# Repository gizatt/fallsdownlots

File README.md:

# FallsDownLots

<details>
  <summary>Click to expand more demo GIFs</summary>

</details>

## About
This project ("FallsDownLots") is a 2-wheeled balancing robot designed around two brushless DC (BLDC) gimbal motors, controlled with field-oriented control. Previous iterations of wheeled balancing robots I've built have been plagued by issues with poor motor control (primarily backlash, inertia, and friction causing shaky control around the upright fixed point). This project instead uses a high-torque (specifically low KV / high winding count) 3-phase motor, paired with an absolute magnetic encoder to determine the shaft angle, and a 3-phase drive circuit to deliver current. With some pretty simple parts, I've been able to get something pretty close to actual torque control for the wheels of this robot, and it's been pretty easy to tune up for smooth, stable, remote-controllable operation.

For ease of control tuning, I chose a main board with Bluetooth Low-Energy (BLE) support, and written a companion program that connects to the robot and allows parameter updates. This program is currently very primitive but it beats reprogramming or having it drag around a serial cable (which interferes with control).

I mostly rely on [SimpleFOC](https://simplefoc.com/) for the actual FOC implementation, and took their advice on sensor and drive chip choice. I'd like to dive deeper into controlling these motors better -- for example, trying to compensate for cogging torque to get smoother operation - but I have more fundamental issues to fix first (see below).

- For code, see the `fallsdownlots` subdirectory (which is a PlatformIO package).
- For CAD, see [Onshape](https://cad.onshape.com/documents/34e0d9ef519aef4b34c19df6/w/b4fc20d7f51a03280199ecb2/e/801a65f226a9bb9fc692247b?renderMode=0&uiState=648a75b56f21326dd5086d67). Sorry it's not organized into a main assembly yet, this is just my 3D print part workshop. Approximately up-to-date STLS are in the `stls` subdirectory. Print `MotorMount` twice, mirroring one of them. Print `Wheel` twice. Print `Tire` twice in TPU or another tacky, flexible filament.
- For PCB design and electrical schematics, see `board_v2` subdirectory (which is a KiCad project).

## Diagram and Parts List

(Note: this references a special-edition physically packaged version of this robot.)

Parts list:
- 2X PLA wheel with TPU tire
- 2x Motor assembly, composed of...
  - 1x PLA Wheel + TPU tire
  - 1x PLA Motor Mount
  - 1x AS5600 Breakout Board
  - 1X 2204-260KV BLDC Motor (with 3-pin JST RE connector)
  - 1X 10KOhm Thermistor
  - 1X JST MX 6-pin Male Connector
- 1x Altoid tin case with lid, containing...
  - 1x PLA board mounting backplate, already attached to case.
  - 1x Main electronics board
  - 4x M3x8mm hex bolts and nuts
  - 8x M2x4mm hex bolts
  - 3x M2x8mm self-tapping phillips screws
  - Spare parts: M3x8mm self-tapping phillips screws, plus other screw types, plus spare TPU tire

Not included (supply seperately):
- 1x 400Mah 2S LiPO [[Amazon link](https://www.amazon.com/gp/product/B072BH1XP6/ref=ox_sc_act_title_1?smid=A10R5CWYCW5T5E&psc=1)] and balance charger.
- 1.5 and 2.5 metric alley keys
- Small phillips head screwdriver
- Small narrow / needle-nose pliers
- Non-ancient bluetooth adapter (probably needs BLE >= 5.1?)

## Assembly Instructions

Assembly is simple, but the tight packaging makes assembly pretty order-sensitive.

1) Attach the motor assemblies onto the bottom of the case, as shown, using 4x M3x8mm hex bolts and nuts. Before you fully attach these, pass their wires into the case through the nearby holes; otherwise it'll be a tight fit to get those wires passed in, especially with the electronics board mounted. Be reasonably gentle with the wires...

2) Now install the main electronics board by sliding it into place and installing the 3x M2x8mm self-tapping phillips screws, which screw into posts on the PLA backplate. Note that you want the wires from the motor assemblies *over* the main board once it's installed -- it's a bit of dance to get it everything into place.
3) Plug in the wires from the motor assemblies into the plugs on their corresponding side. See picture for exact orientation of wires -- carefully note the orientation of the 3-pin motor connectors! If you get this backwards, the motors will spin the wrong way. I recommend some good needlenose pliers to help with wrangling and attaching these cables.

4) Attach the tires to the motors with at least 2x M2x4mm hex bolts each. These bolts should be snug but don't go ham (the PLA may not be able to take it).
5) Slide the battery into the space under the on-off switch with the cables facing left, and plug in the cable, being careful to have the red wire on the right. *This board technically has reverse bias protection but I have never tested it and I do not want you to either.*

Troubleshooting: contact me!

### Motor assembly internals

I packaged this robot with each motor and sensor already assembled, since their assembly is a bit sensitive, but you're welcome to disassemble and take a look. These assemblies are pancakes of a tiny BLDC motor ([Amazon link](https://www.amazon.com/DAUERHAFT-Brushless-Efficiency-Drones-Gimbal/dp/B08S5JSD3Q/ref=sr_1_4?crid=16NAYMQDO30CI&keywords=bldc+8605&qid=1686794765&sprefix=bldc+860%2Caps%2C130&sr=8-4), though this unit is much cheaper on Aliexpress) with a magnet superglued to its shaft, an [absolute magnetic encoder](https://www.amazon.com/Magnetic-Encoder-Induction-Measurement-Precision/dp/B094F8H591/ref=sr_1_2?crid=1PB3J5XDUXQNP&keywords=magnetic+encoder&qid=1686794826&sprefix=magnetic+encod%2Caps%2C122&sr=8-2) on a breakout board, and a thermistor sandwiched between them.

## Usage instructions

Flip the switch to the right to turn on. I recommend laying the robot down or standing it on its head during startup; each wheel will independent move a quarter rotation back and forth during startup as a calibration routine (this is managed by SimpleFOC). Once that is done, the robot should be active, and will attempt to balance to the upright if it is within ~60 degrees of upright. The easiest way to get it going is to go to a clear area of floor, holding it sideways, and confidentally and quickly place it roughly upright and let go. The integrators reset and motors turn off again when it is not upright, e.g. if it falls.

I recently discovered another fun demo method that happens to work, despite the control algorithm not being created with this in mind: hold the robot by the wheels, and swing the robot upright. It should catch itself at the upright and stabilize there. See [this video](media/flipup_demo.gif).

Note: there's a few bugs somewhere in the code, especially in the BLE stuff, and sometimes the IMU or magnetic encoders get into weird states and stop talking. If the robot suddenly stops and falls over, or otherwise seems unresponsive, just do a complete power cycle. This is more likely to happen if you're using one of the BLE scripts, proportional to how much data you're sending/receiving.

## Control details

The main control code is implemented in `main-fallsdownlots.cpp::do_control`. I'm currently running a PID loop on angle, with the zero angle estimated via a low-pass filter on the measured angle (which assumes we stabilize on average to the upright), plus a PI loop on wheel velocity, plus a PI loop on yaw velocity. These are all controlled by parameters in the `ControlParams` struct.

There are two Python scripts in the `fallsdownlots/scripts` folder. Both connect to the robot with BLE.
- `communicator.py`: Once connected, type a command of the format "<param name> <float value>" and hit enter, and it'll send it to the robot. It should echo the new setting back, though sometimes it takes a while to come back. If you just send "<param name>" without a value, it'll send the current value back. Example: "ANG_D 0.1" changes the derivative gain to 0.1. Ignore the plot window that opens up, it doesn't work yet...
- `gamepad.py`: Connects to the robot and sends commands (adjusting the setpoints of the velocity and yaw velocity control loops) in response to the arrow keys, letting you control the robot. Hold shift while pressing arrow keys to go faster. There's a mode to display robot odometry (see code) but it's currently super sketchy.

## Notes / Thoughts

### TODOs
- Major code cleanup. Tons of cruft left here I haven't re-orged.
- Use BLE interface to create an interactive motor teststand for tuning up actual motor control loops.

### Stuff that didn't work as well as I hoped
- Because I'm talking to 2 magnetic encoders and 1 IMU over relatively slow I2C (800khz, I think), I haven't been able to get my main control loop to run faster than ~200hz. I'm configuring the IMU to do its own high-rate on-board orientation estimation, so that's fine -- but this low rate makes it hard to drive the motors in anything other than torque mode (velocity and position mode go unstable pretty easily / can't be tuned to be too accurate as my loop rate is probably too low), and I can't crank the actual control gains as high as I'd like for tight tracking without inducing oscillations. It's possible I can get info from at least the magnetic encoders over their analog output instead... but I would need to experiment with that.
- I'm relying on Bluetooth Low-Energy as my wireless comms media, but I'm finding the bandwidth super low, and the code on the embedded side super crash-prone. I'm probably overloading buffers somewhere and configuring stuff wrong... next time, I'm just gonna have the robot connect to my Wifi. I'd rather deal with networking gremlins I sort of understand than BLE ones I don't.

### BLE Comms Protocol

The robot sends a 36-byte (+COBS-encoding) packet over BLE UART at ~30hz consisting of 8 floats:
```
[pitch, yaw, d_pitch, d_yaw, odometry, l_cmd, r_cmd, max_motor_temp]
```

On-board, the robot has a registry of named control parameters that you can write with a command formatted:
```
<NULL-TERMINATED-NAME>[optional single float]
```
and the robot will respond with a similarly formatted message (+COBS-encoding) packet with a single float indicating the updated value, or the current value if you didn't include the float value.

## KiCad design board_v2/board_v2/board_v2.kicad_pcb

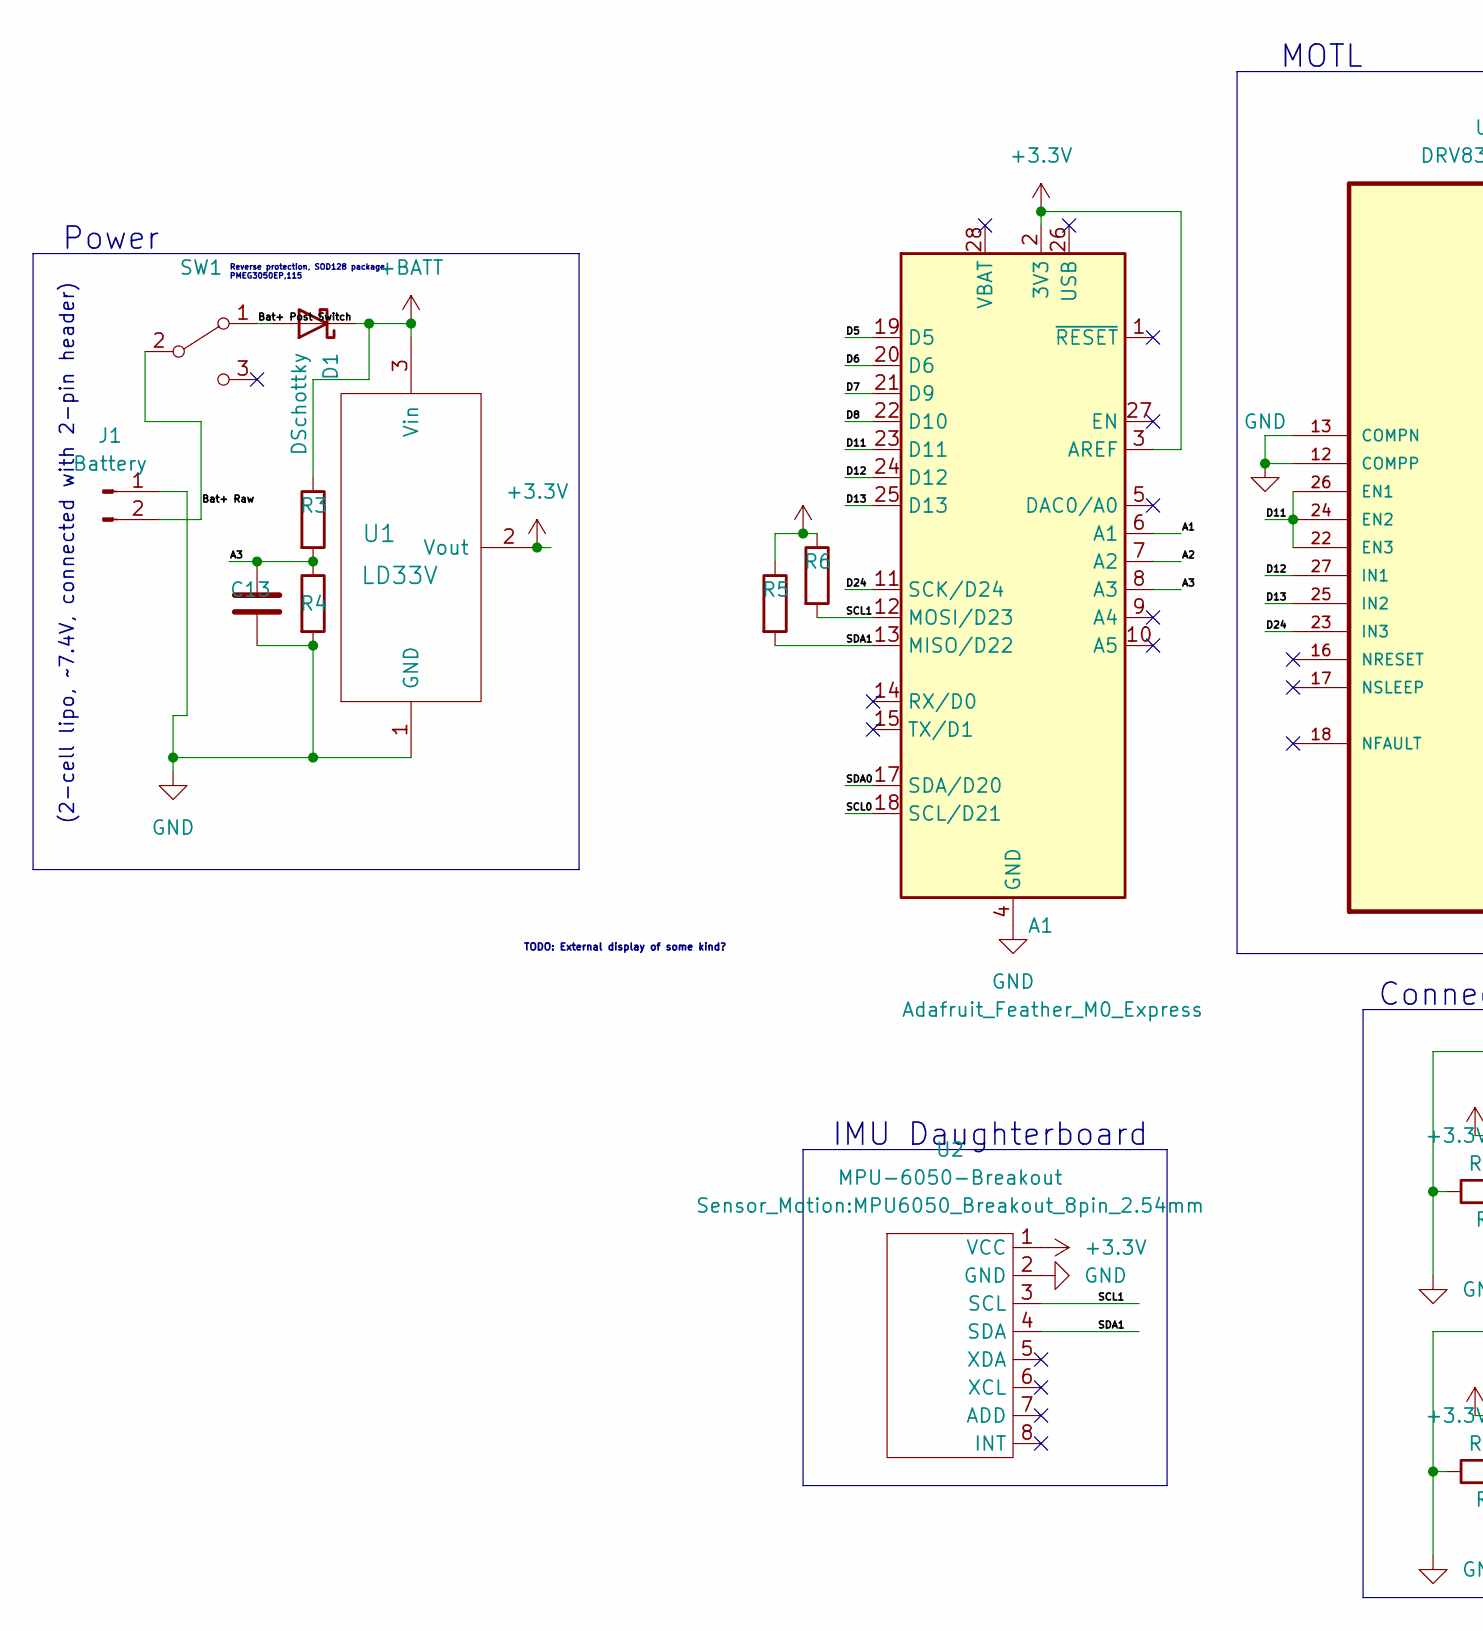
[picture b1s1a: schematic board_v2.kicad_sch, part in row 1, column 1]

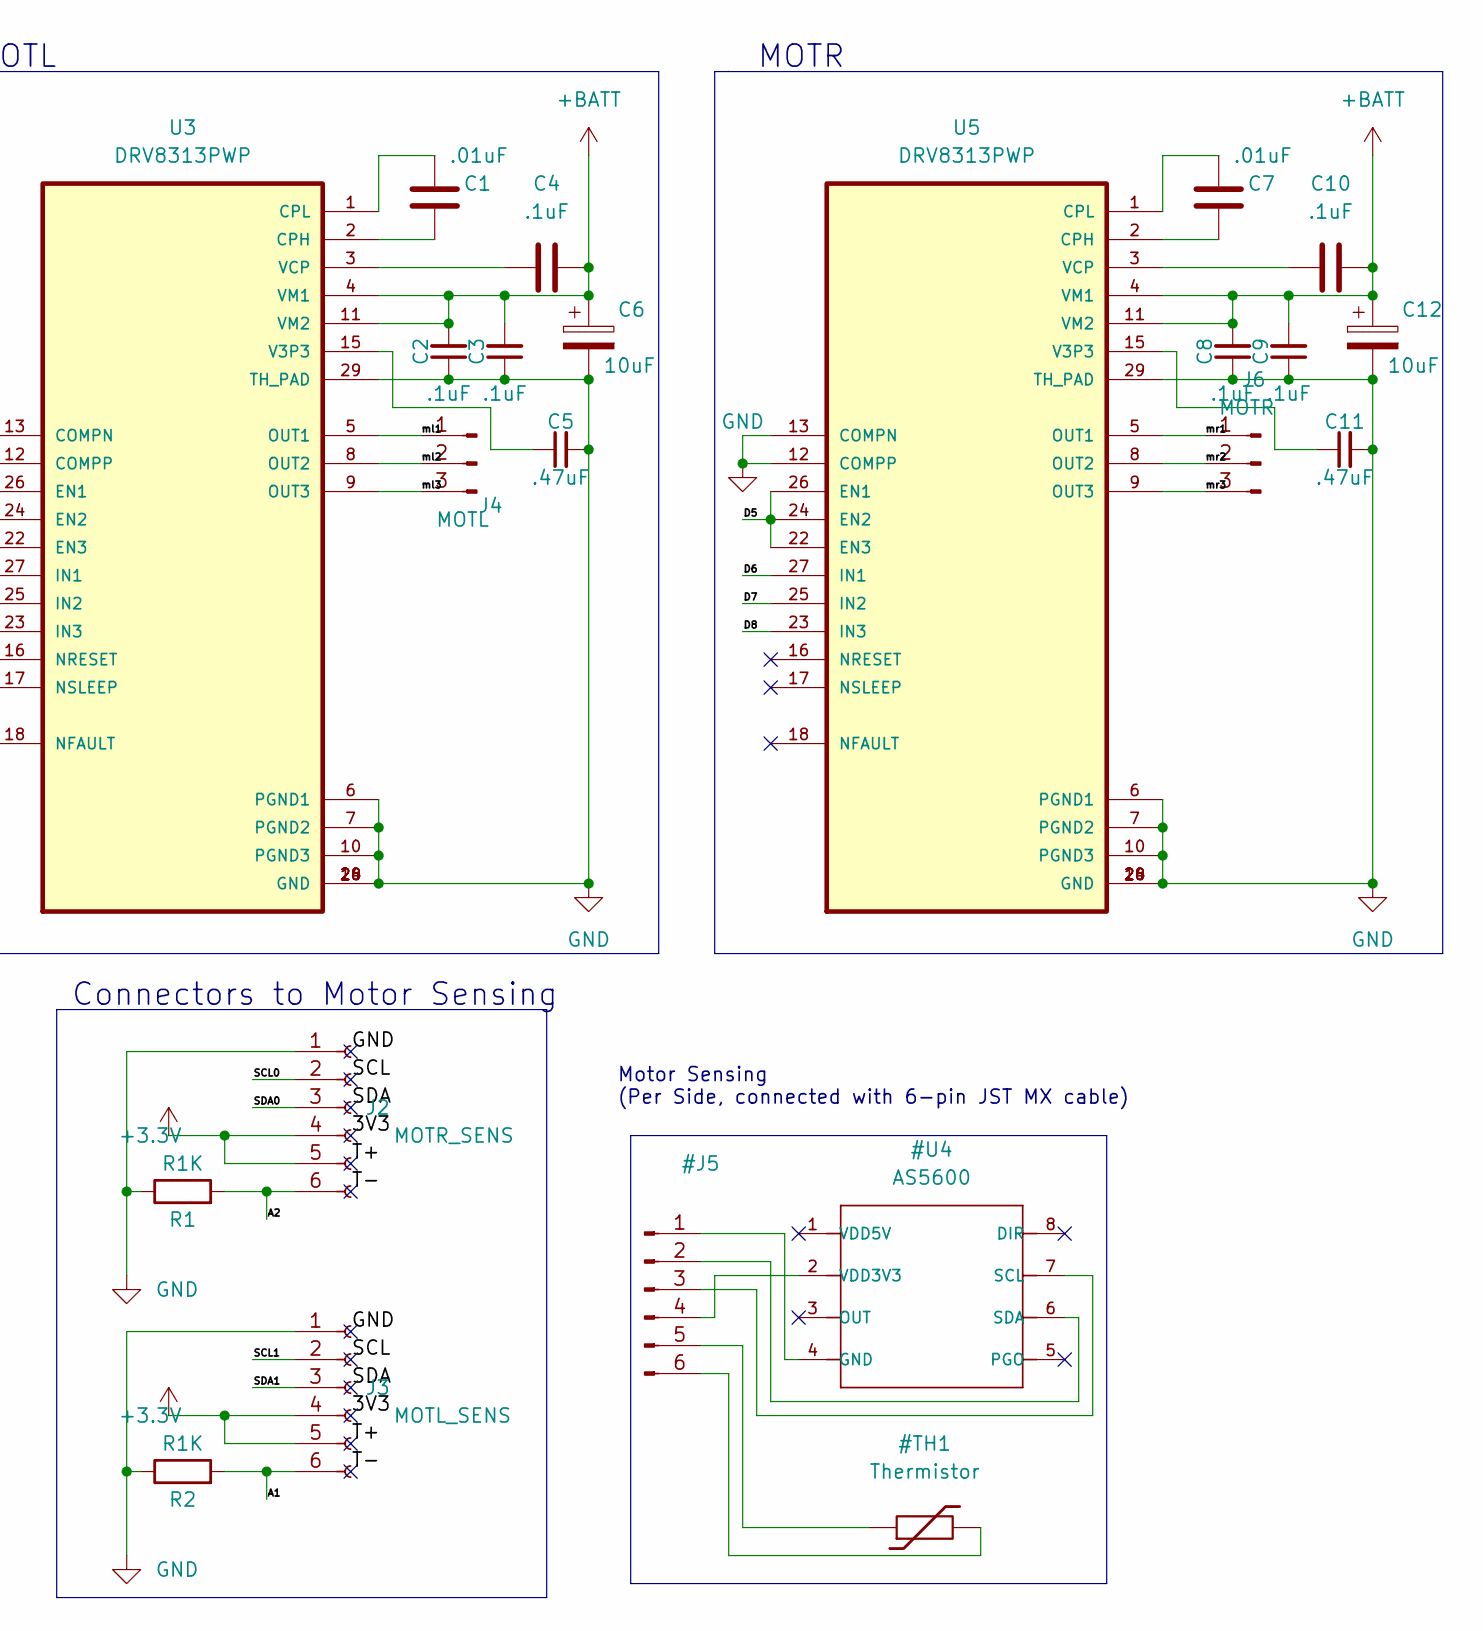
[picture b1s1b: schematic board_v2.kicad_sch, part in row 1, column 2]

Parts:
A1: Adafruit_Feather_M0_Express; Adafruit_Feather_M0_Wifi_WithMountingHoles
C1, C7: .01uF; C_0805_2012Metric_Pad1.18x1.45mm_HandSolder
C2, C3, C4, C8, C9, C10: .1uF; C_0805_2012Metric_Pad1.18x1.45mm_HandSolder
C5, C11: .47uF; C_0805_2012Metric_Pad1.18x1.45mm_HandSolder
C6, C12: 10uF; CP_Radial_D5.0mm_P2.50mm
C13: (no value)
D1: DSchottky; D_SOD-128
J1: Battery; PinHeader_1x02_P2.54mm_Horizontal
J2: MOTR_SENS; JST MX x6
J3: MOTL_SENS; JST MX x6
J4: MOTL; PinHeader_1x03_P2.54mm_Horizontal
J6: MOTR; PinHeader_1x03_P2.54mm_Horizontal
R1, R2: R1K; R_0805_2012Metric_Pad1.20x1.40mm_HandSolder
R3, R4, R5, R6: (no value)
SW1: (no value)
U1: LD33V; TO-220-3_Horizontal_TabDown
U2: MPU-6050-Breakout; MPU6050_Breakout_8pin_2.54mm
U3, U5: DRV8313PWP; IC_TPS61196PWPRQ1

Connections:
+BATT: C2.2, C3.2, C4.2, C6.1, C8.2, C9.2, C10.2, C12.1, D1.1 (K), R3.1, U1.3 (Vin), U3.4 (VM1), U3.11 (VM2), U5.4 (VM1), U5.11 (VM2)
/A1: A1.6 (A1), J3.6, R2.2
/A2: A1.7 (A2), J2.6, R1.2
/A3: A1.8 (A3), C13.1, R3.2, R4.1
/Bat+ Post Switch: D1.2 (A), SW1.1 (A)
/Bat+ Raw: J1.2, SW1.2 (B)
/D5: A1.19 (D5), U5.22 (EN3), U5.24 (EN2), U5.26 (EN1)
/D6: A1.20 (D6), U5.27 (IN1)
/D7: A1.21 (D9), U5.25 (IN2)
/D8: A1.22 (D10), U5.23 (IN3)
/D11: A1.23 (D11), U3.22 (EN3), U3.24 (EN2), U3.26 (EN1)
/D12: A1.24 (D12), U3.27 (IN1)
/D13: A1.25 (D13), U3.25 (IN2)
/D24: A1.11 (SCK/D24), U3.23 (IN3)
/SCL0: A1.18 (SCL/D21), J2.2
/SCL1: A1.12 (MOSI/D23), J3.2, R6.2, U2.3 (SCL)
/SDA0: A1.17 (SDA/D20), J2.3
/SDA1: A1.13 (MISO/D22), J3.3, R5.2, U2.4 (SDA)
/ml1: J4.1, U3.5 (OUT1)
/ml2: J4.2, U3.8 (OUT2)
/ml3: J4.3, U3.9 (OUT3)
/mr1: J6.1, U5.5 (OUT1)
/mr2: J6.2, U5.8 (OUT2)
/mr3: J6.3, U5.9 (OUT3)
GND: A1.4 (GND), A1.16 (GND), C2.1, C3.1, C5.2, C6.2, C8.1, C9.1, C11.2, C12.2, C13.2, J1.1, J2.1, J3.1, R1.1, R2.1, R4.2, U1.1 (GND), U2.2 (GND), U3.6 (PGND1), U3.7 (PGND2), U3.10 (PGND3), U3.12 (COMPP), U3.13 (COMPN), U3.14 (GND), U3.20 (GND), U3.28 (GND), U3.29 (TH_PAD), U5.6 (PGND1), U5.7 (PGND2), U5.10 (PGND3), U5.12 (COMPP), U5.13 (COMPN), U5.14 (GND), U5.20 (GND), U5.28 (GND), U5.29 (TH_PAD)
unnamed: C1.1, U3.1 (CPL)
unnamed: C1.2, U3.2 (CPH)
unnamed: C4.1, U3.3 (VCP)
unnamed: C5.1, U3.15 (V3P3)
unnamed: C7.1, U5.1 (CPL)
unnamed: C7.2, U5.2 (CPH)
unnamed: C10.1, U5.3 (VCP)
unnamed: C11.1, U5.15 (V3P3)

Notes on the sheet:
Power
TODO: External display of some kind?
IMU Daughterboard
MOTL
Motor Sensing (Per Side, connected with 6-pin JST MX cable)
MOTR
(2-cell lipo, ~7.4V, connected with 2-pin header)
Connectors to Motor Sensing
Reverse protection, SOD128 package, PMEG3050EP,115

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
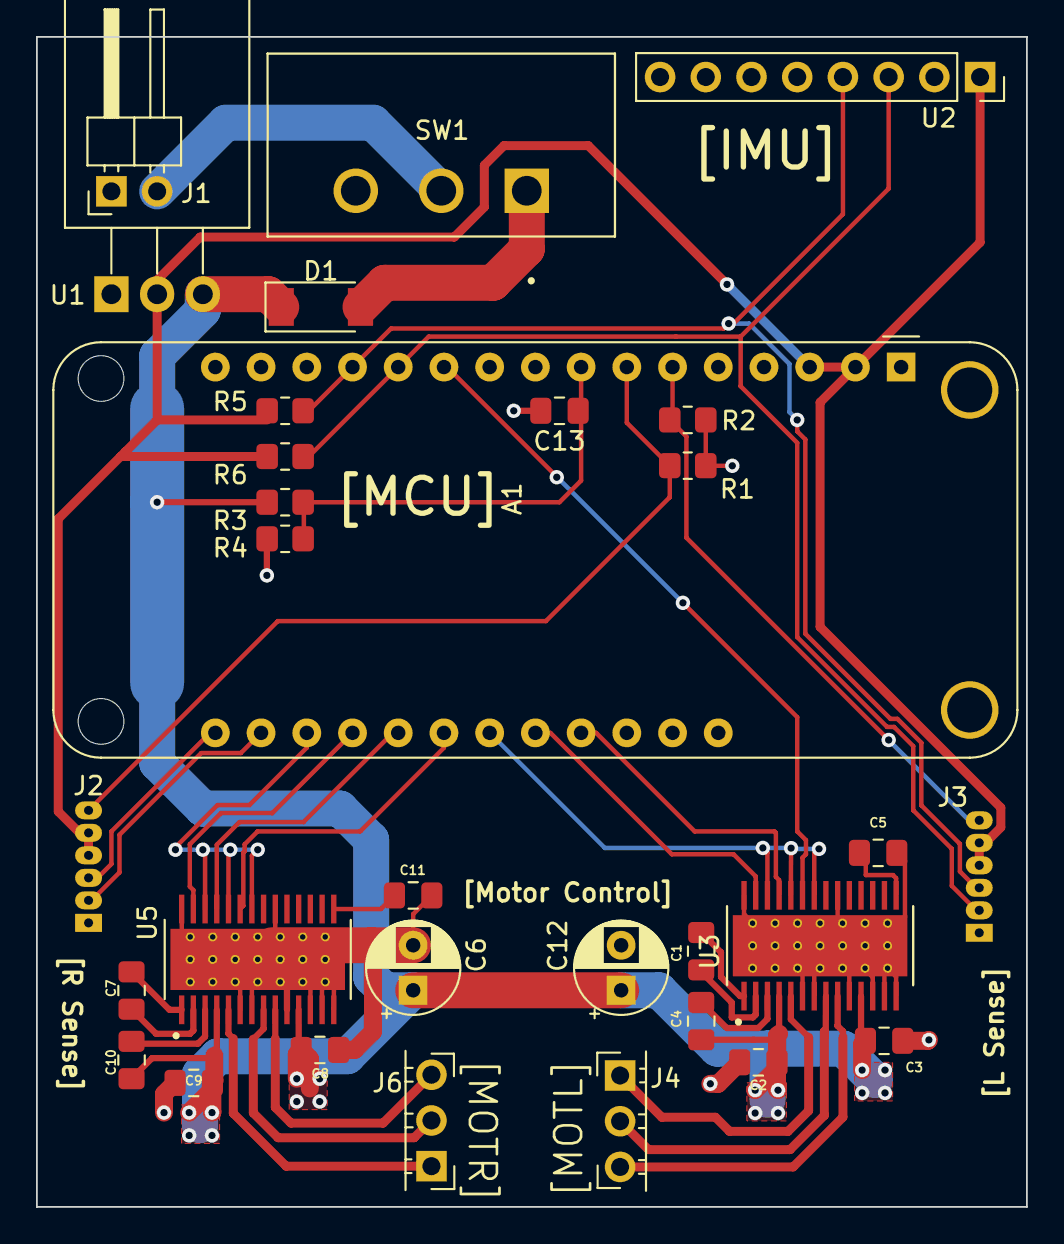
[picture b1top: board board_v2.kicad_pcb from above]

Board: 2 copper layers, 55.0 x 65.0 mm, 31 parts (0 on the bottom side), 34 nets.

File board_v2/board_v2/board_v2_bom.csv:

"Source:","C:\Users\Greg Izatt\src\fallsdownlots\board_v2\board_v2\board_v2.kicad_sch"
"Date:","6/4/2023 8:46:51 PM"
"Tool:","Eeschema 7.0.1"
"Generator:","C:\Program Files\KiCad\7.0\bin\scripting\plugins/bom_csv_grouped_by_value.py"
"Component Count:","35"

"Collated Components:"

"Item","Qty","Reference(s)","Value","LibPart","Footprint","Datasheet","DNP"
"1","1","A1","Adafruit_Feather_M0_Express","MCU_Module:Adafruit_Feather_Generic","Module:Adafruit_Feather","https://cdn-learn.adafruit.com/downloads/pdf/adafruit-feather.pdf",""
"2","2","C1, C7",".01uF","Device:C","Capacitor_SMD:C_0805_2012Metric_Pad1.18x1.45mm_HandSolder","~",""
"3","4","C2, C3, C8, C9",".1uF","Device:C_Small","Capacitor_SMD:C_0805_2012Metric_Pad1.18x1.45mm_HandSolder","~",""
"4","3","C4, C10, C13",".1uF","Device:C","Capacitor_SMD:C_0805_2012Metric_Pad1.18x1.45mm_HandSolder","~",""
"5","2","C5, C11",".47uF","Device:C_Small","Capacitor_SMD:C_0805_2012Metric_Pad1.18x1.45mm_HandSolder","~",""
"6","2","C6, C12","10uF","Device:C_Polarized","Capacitor_THT:CP_Radial_D5.0mm_P2.50mm","~",""
"7","1","D1","DSchottky","Device:D_Schottky","Diode_SMD:D_SOD-128","~",""
"8","1","J1","Battery","Connector:Conn_01x02_Male","Connector_PinHeader_2.54mm:PinHeader_1x02_P2.54mm_Horizontal","~",""
"9","1","J2","MOTR_SENS","Connector:Conn_01x06_Female","Connector:JST MX x6","~",""
"10","1","J3","MOTL_SENS","Connector:Conn_01x06_Female","Connector:JST MX x6","~",""
"11","1","J4","MOTL","Connector:Conn_01x03_Male","Connector_PinHeader_2.54mm:PinHeader_1x03_P2.54mm_Horizontal","~",""
"12","1","J6","MOTR","Connector:Conn_01x03_Male","Connector_PinHeader_2.54mm:PinHeader_1x03_P2.54mm_Horizontal","~",""
"13","2","R1, R2","R1K","Device:R","Resistor_SMD:R_0805_2012Metric_Pad1.20x1.40mm_HandSolder","~",""
"14","1","R3","1M","Device:R","Resistor_SMD:R_0805_2012Metric_Pad1.20x1.40mm_HandSolder","~",""
"15","1","R4","470K","Device:R","Resistor_SMD:R_0805_2012Metric_Pad1.20x1.40mm_HandSolder","~",""
"16","6","R5, R6, R7, R8, R9, R10","R10K","Device:R","Resistor_SMD:R_0805_2012Metric_Pad1.20x1.40mm_HandSolder","~",""
"17","1","SW1","SW_SPDT","Switch:SW_SPDT","downloaded:SW_L102021ML04Q","~",""
"18","1","U1","LD33V","ld33v:LD33V","Package_TO_SOT_THT:TO-220-3_Horizontal_TabDown","",""
"19","1","U2","MPU-6050-Breakout","Sensor_Motion:MPU-6050-Breakout","Sensor_Motion:MPU6050_Breakout_8pin_2.54mm","",""
"20","2","U3, U5","DRV8313PWP","DRV8313PWP:DRV8313PWP","downloaded:IC_TPS61196PWPRQ1","",""

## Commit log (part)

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2022-05-02 First iteration; 3d printed body with a tiny gear motor from amazon.
2022-05-03 Stepper motor control!
    Maxes at about 2khz
2022-05-03 Now it plays happy birthday
2022-05-03 Revert "Now it plays happy birthday"
    This reverts commit 46fa420b528191eefaf3d61706d850ea1cae0c28.
2022-05-03 IMU drives motor
2022-05-06 Schematic update to stepper
2022-05-06 V2 body
2022-05-06 Prototype speed ramping... doesnt seem to help much.
2022-05-06 Revert "Prototype speed ramping... doesnt seem to help much."
    This reverts commit a9c41792ba803ab4711aafc375a5761d031a6a4b.
2022-05-21 Better logging and IMU filtering, but not good enough.
2022-05-21 Try SimpleFOC stepper driver. Doesn't work well at high speeds... badly configured?
2022-05-21 Revert "Try SimpleFOC stepper driver."
    This reverts commit eb4803a5b4304382071dabc3fbd5138f6ade1855.
2022-05-22 Janky hand-written PWM for smoother motor
2022-05-22 Config that kind of stands!
2022-05-23 Current config
2022-05-23 Changing to clearer state space PD control.
2022-05-25 Configuration that works! Swapping battery for a 7V lipo was critical
2023-03-21 checkin before swap off of due
2023-04-01 Check in state before computer move
2023-05-25 Working ver
2023-05-25 Working BLE and FOC for v2
2023-05-25 Update V2 board schematics
2023-05-29 Break out thremistor code to its own class and fix it up.
2023-05-29 BLE communication established
2023-05-29 Basic stabilizing params!
2023-05-29 Add simple odom-based terms
2023-06-04 Tune up BLE a bit
2023-06-04 Fix remaining bugs in param-seting protocol
2023-06-05 BOM re-export
2023-06-05 IMU changes, yaw control
2023-06-05 More precisely named integrators.
2023-06-05 Simple remote control with keyboard
2023-06-07 Bandwidth greatly improved
2023-06-07 Plotting tweaks
2023-06-14 Final tweaks
2023-06-15 Major readme update
2023-06-15 Big cleanup
2023-06-15 STLs
2023-06-15 Add sheet to print
2023-06-19 gSTLs
2023-06-19 Flesh out README with demo videos and pictures.
2023-06-20 Typo fix
2026-02-25 Checkin changes
2026-02-25 Claude draft of RL integration doc
2026-02-28 Plan
2026-02-28 Basic layout
2026-04-05 Test of sysid
2026-04-05 Tweaks
2026-04-05 SysID
2026-04-05 Tweak
2026-04-05 Feedforward
2026-04-06 Testing tweaks
2026-04-06 Fixes
2026-04-06 Simpler
2026-04-06 Default gains
2026-04-06 More calib
2026-04-07 Runs
